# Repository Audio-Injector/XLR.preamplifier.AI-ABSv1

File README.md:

XLR preamplifier

A balanced preamplifier based on the Audio Injector Analogue Breakout Standard v1 (AI-ABS v1)

https://github.com/Audio-Injector/AudioInjector-Analogue-Breakout-Standard

https://www.audioinjector.net/xlr-preamp

https://shop.audioinjector.net/detail/Sound_Cards/Balanced+XLR+preamplifier

Check the single ended (RCA) preamplifier here : https://github.com/Audio-Injector/RCA.preamplifier.AI-ABSv1

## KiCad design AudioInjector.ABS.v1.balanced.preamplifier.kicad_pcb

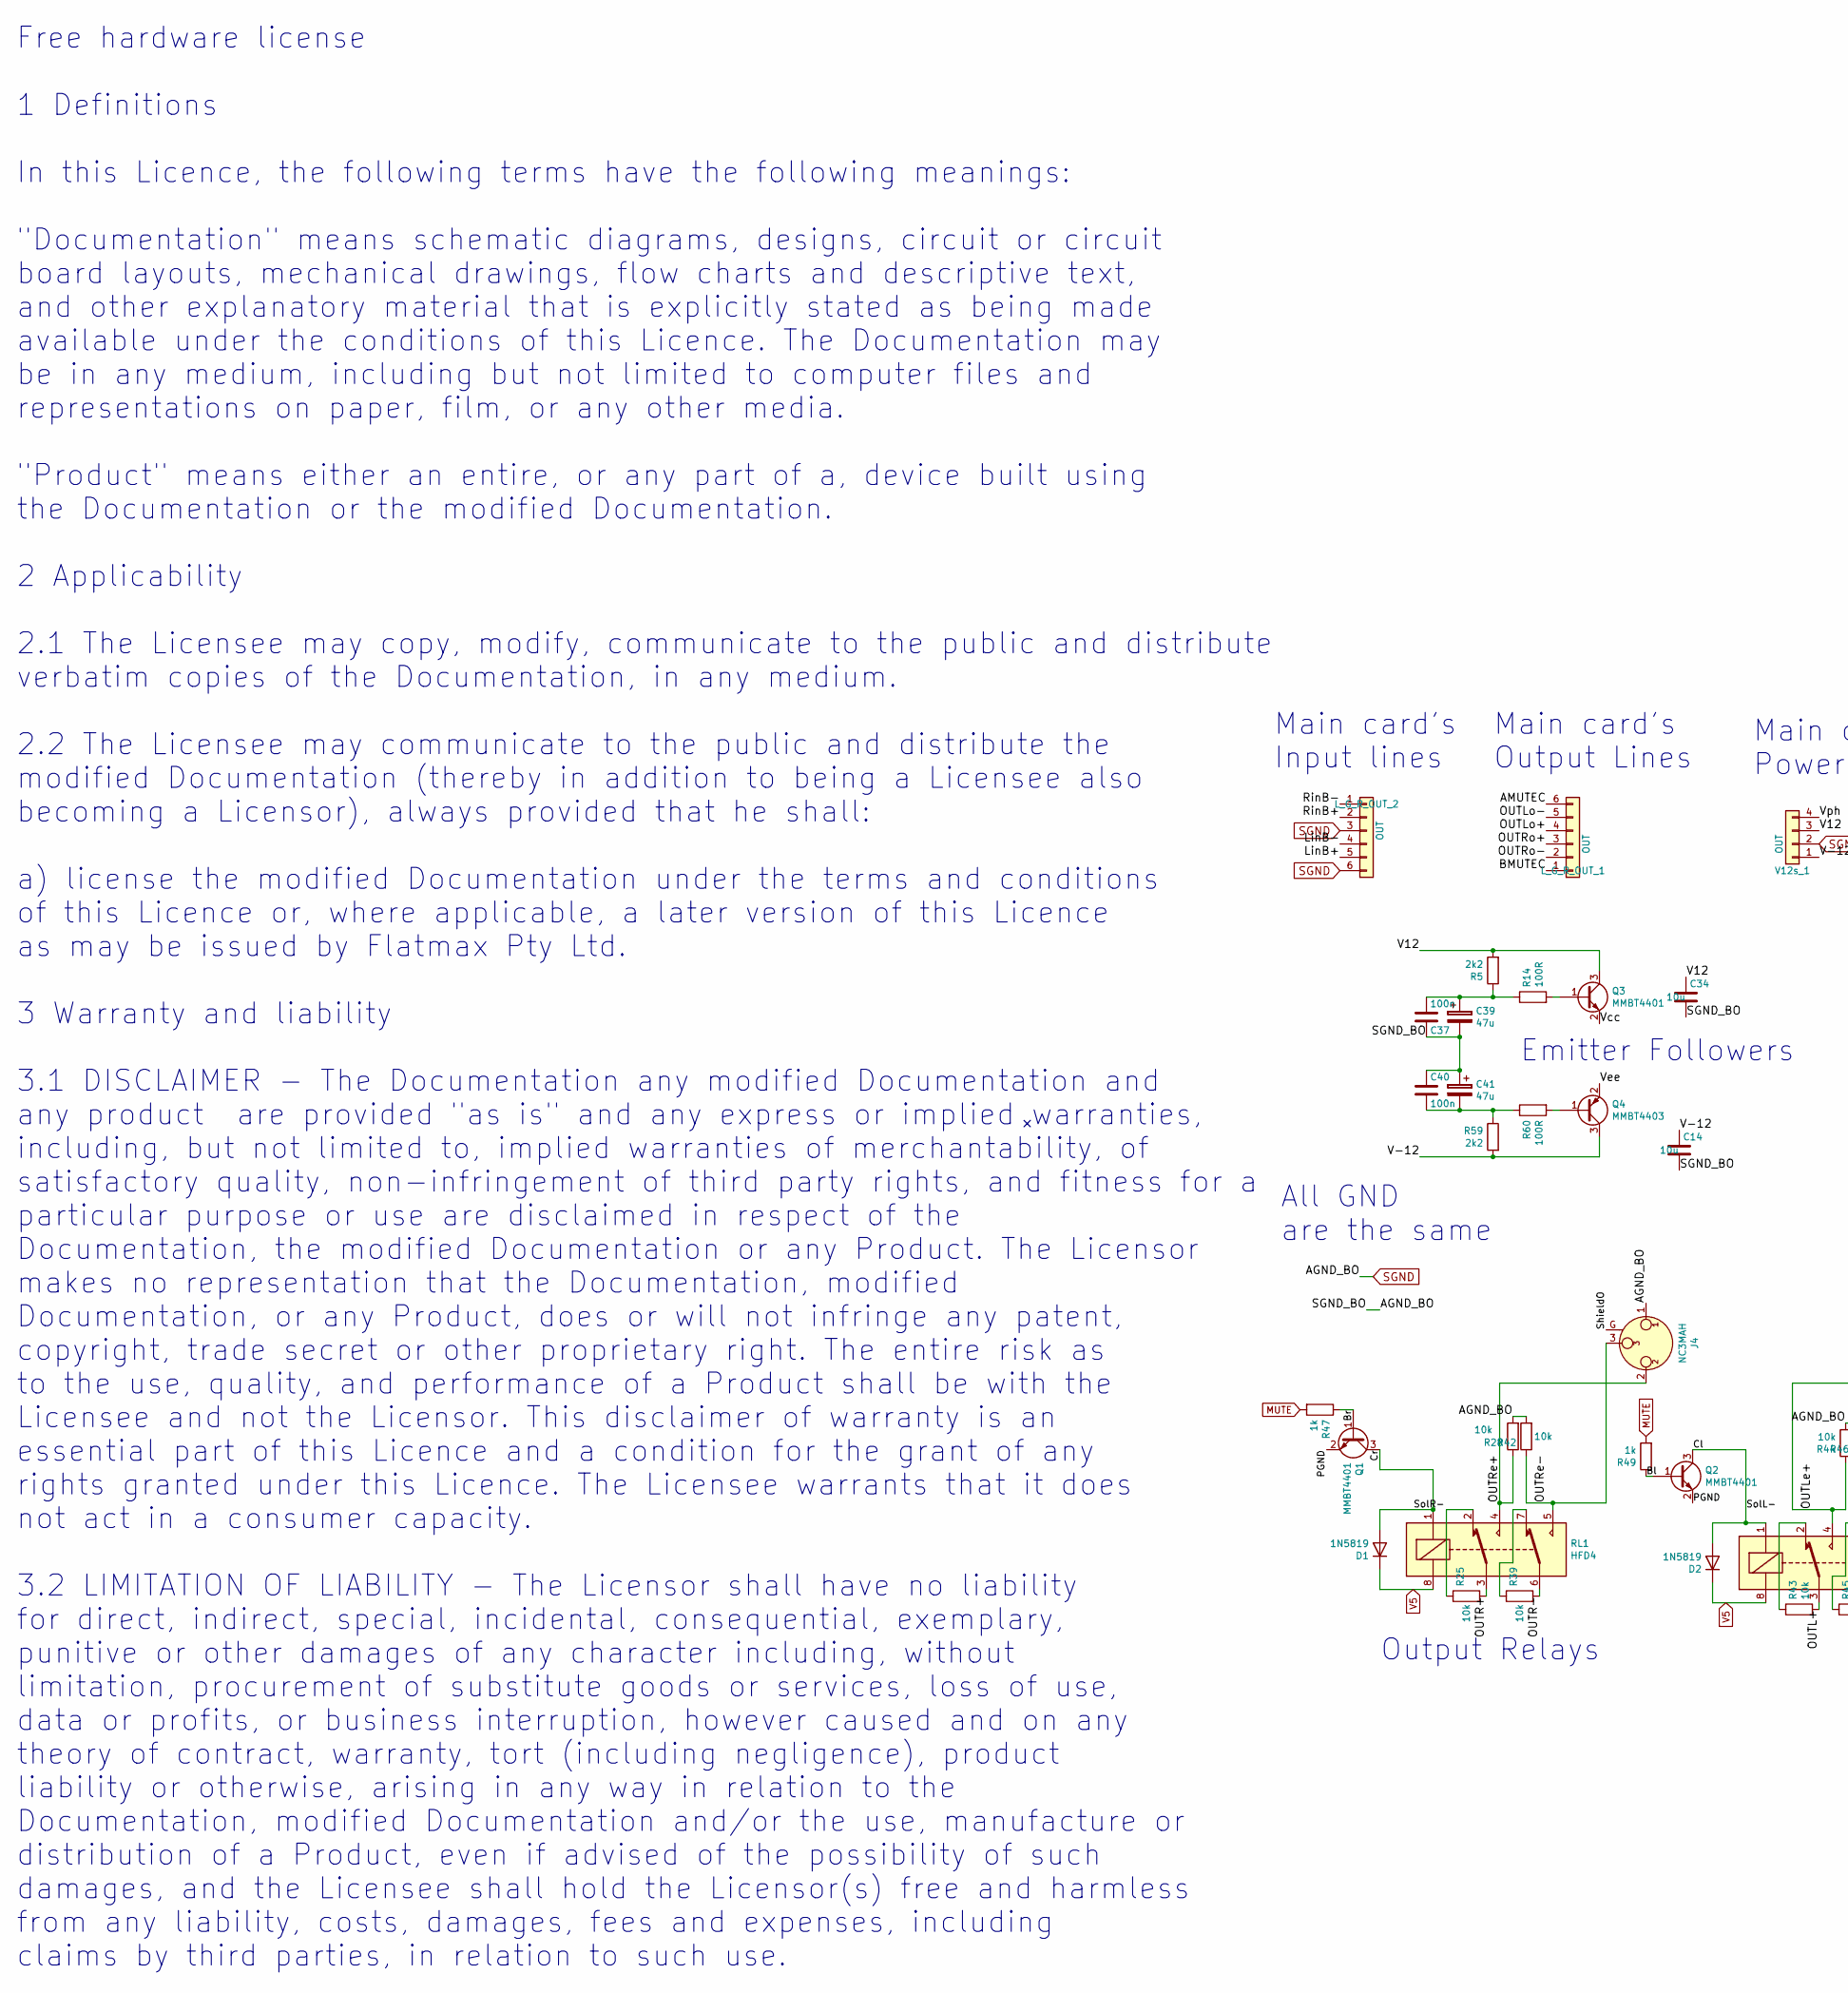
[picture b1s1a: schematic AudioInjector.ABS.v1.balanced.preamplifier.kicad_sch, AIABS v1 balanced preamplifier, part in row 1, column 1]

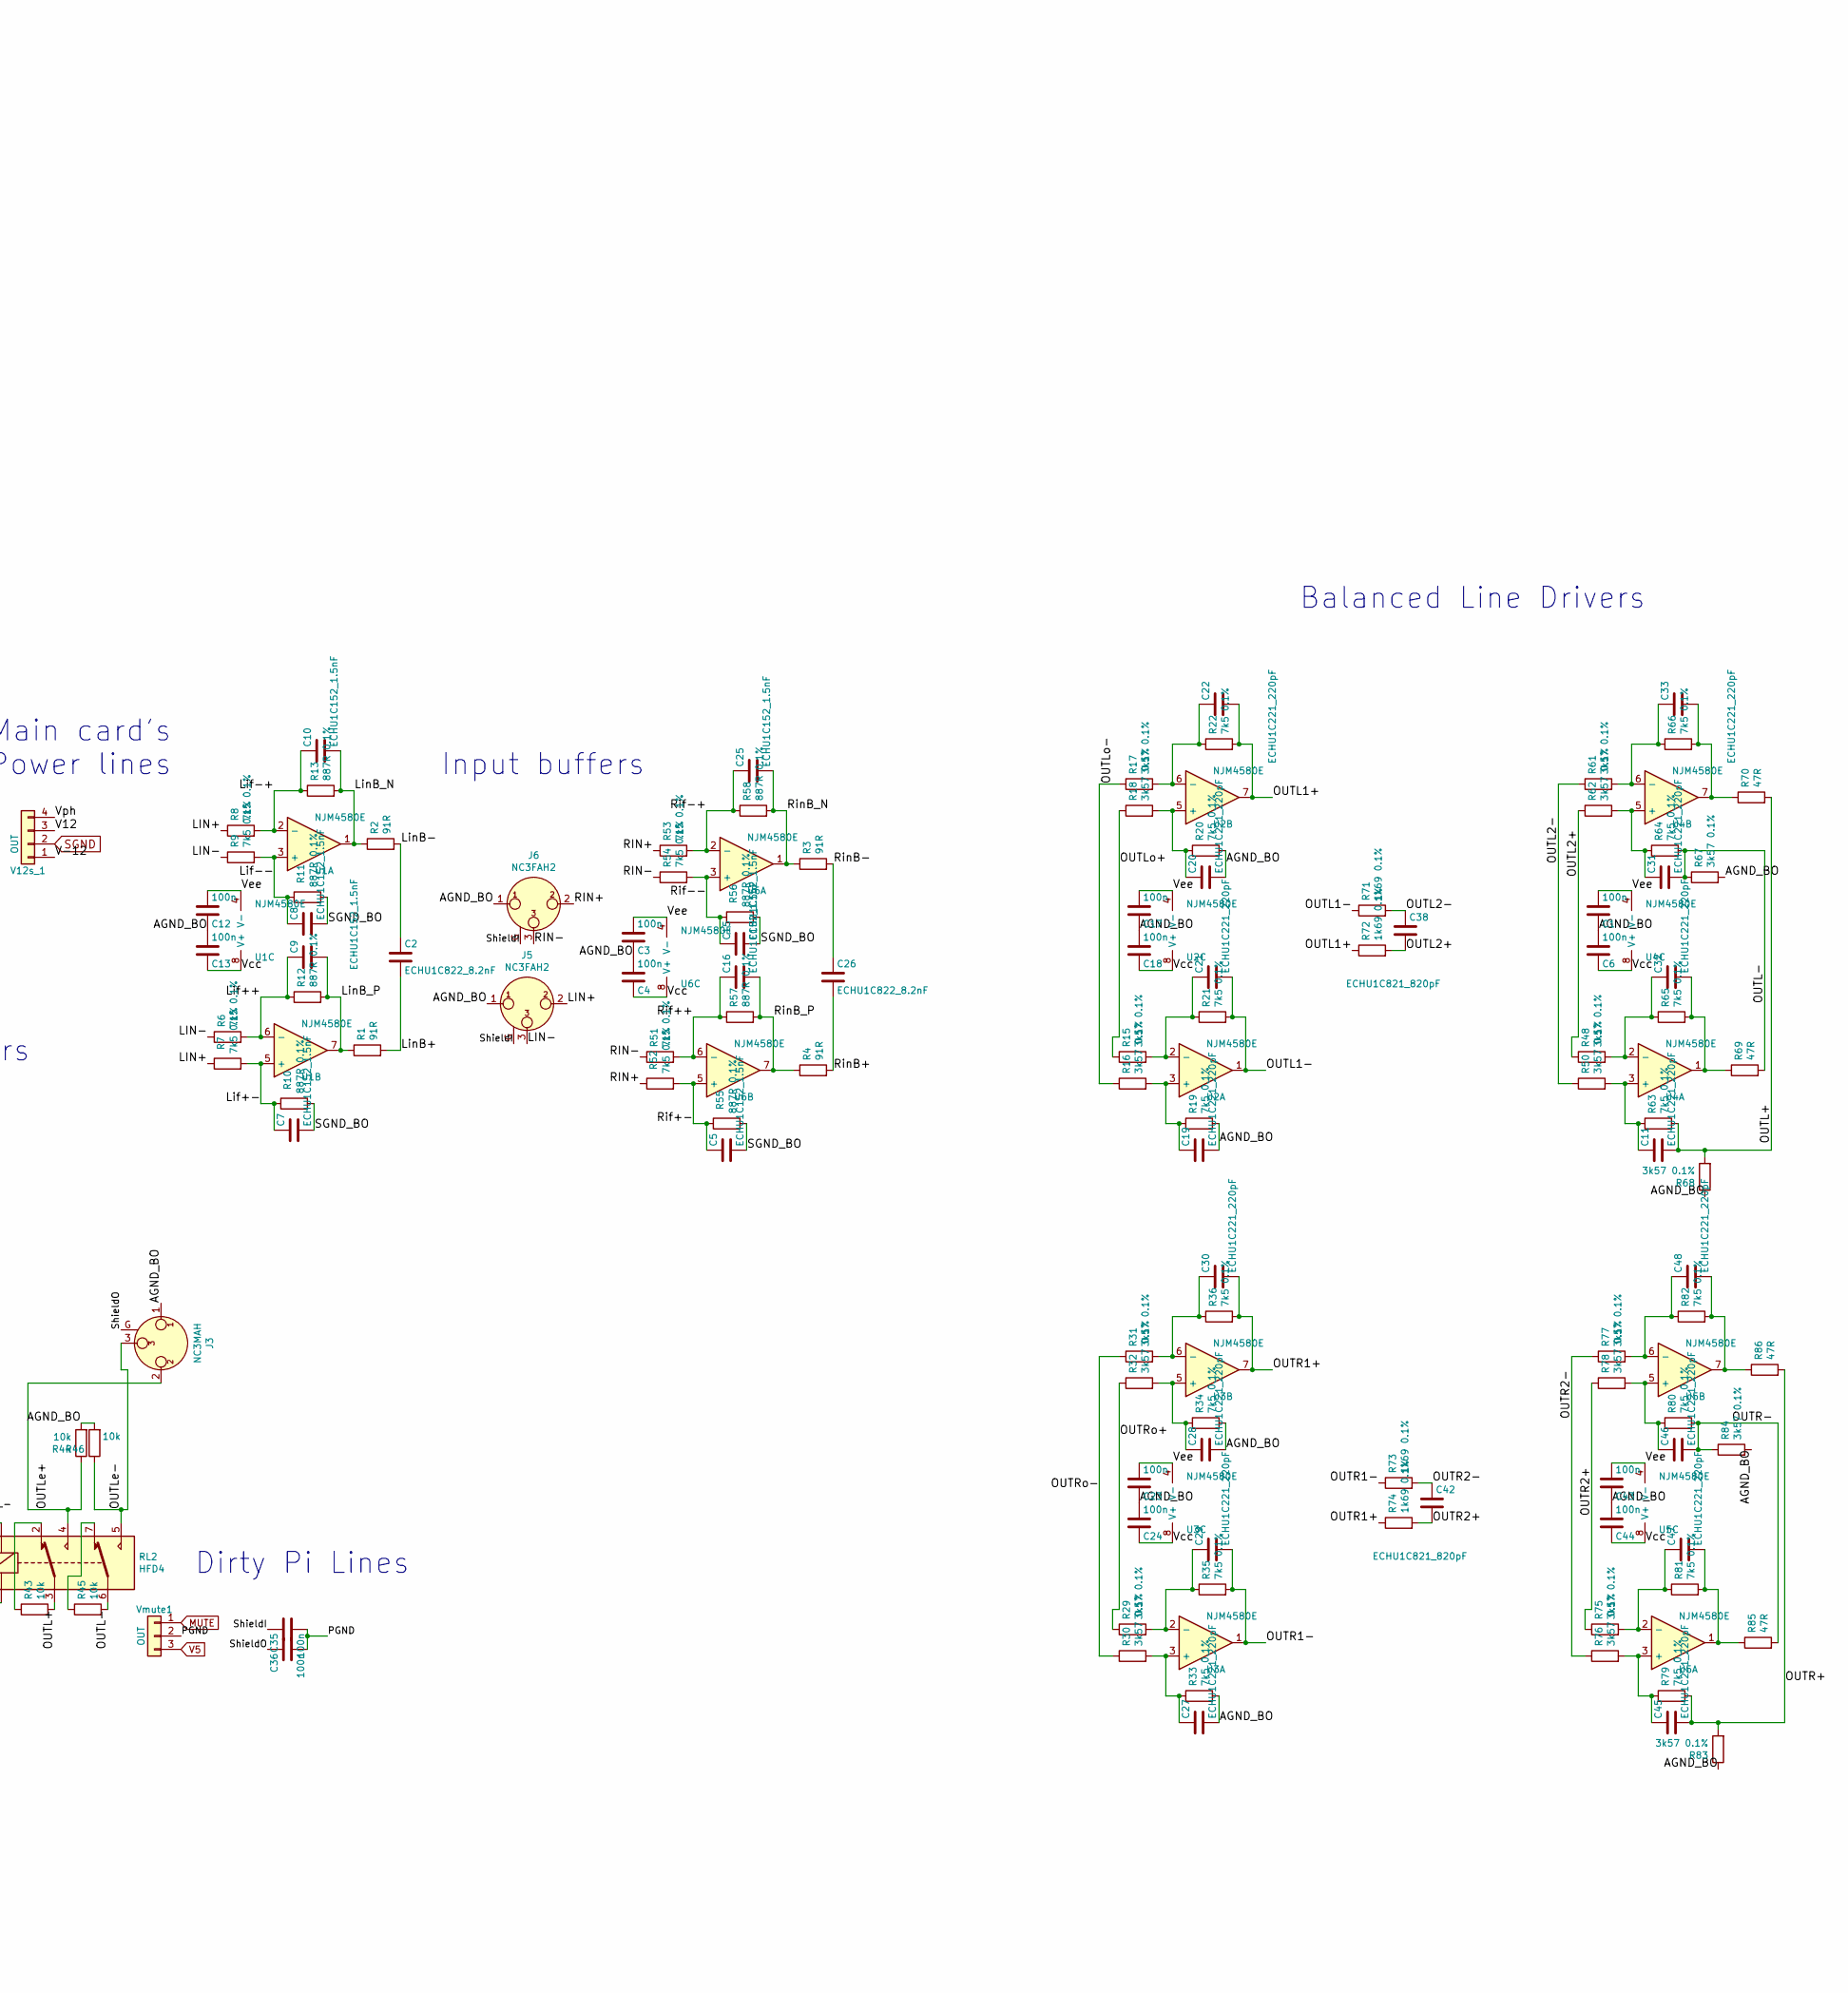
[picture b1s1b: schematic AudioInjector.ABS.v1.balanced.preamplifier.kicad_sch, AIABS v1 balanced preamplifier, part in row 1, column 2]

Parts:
C1, C3, C4, C6, C12, C13, C17, C18, C23, C24, C35, C36, C37, C40, C43, C44: 100n; C_0603_1608Metric
C2, C26: ECHU1C822_8.2nF; C_0805_2012Metric
C5, C7, C8, C9, C10, C15, C16, C25: ECHU1C152_1.5nF; C_0805_2012Metric
C11, C19, C20, C21, C22, C27, C28, C29, C30, C31, C32, C33, C45, C46, C47, C48: ECHU1C221_220pF; C_0805_2012Metric
C14, C34: 10u; C_0805_2012Metric
C38, C42: ECHU1C821_820pF; C_0805_2012Metric
C39, C41: 47u; CP_Elec_6.3x7.7
D1, D2: 1N5819; D_SOD-123
J3, J4: NC3MAH; Jack_XLR_Neutrik_NC3MAH-0_Horizontal
J5, J6: NC3FAH2; Jack_XLR_Neutrik_NC3FAH2_Horizontal
L_G_R_OUT_1, L_G_R_OUT_2: OUT; PinHeader_1x06_P2.54mm_Vertical
Q1, Q2, Q3: MMBT4401; SOT-23
Q4: MMBT4403; SOT-23
R1, R2, R3, R4: 91R; R_0603_1608Metric
R5, R59: 2k2; R_0603_1608Metric
R6, R7, R8, R9, R19, R20, R21, R22, R33, R34, R35, R36, R51, R52, R53, R54, R63, R64, R65, R66, R79, R80, R81, R82: 7k5 0.1%; R_0603_1608Metric
R10, R11, R12, R13, R55, R56, R57, R58: 887R 0.1%; R_0603_1608Metric
R14, R60: 100R; R_0603_1608Metric
R15, R16, R17, R18, R29, R30, R31, R32, R48, R50, R61, R62, R67, R68, R75, R76, R77, R78, R83, R84: 3k57 0.1%; R_0603_1608Metric
R25, R28, R39, R42, R43, R44, R45, R46: 10k; R_0603_1608Metric
R47, R49: 1k; R_0603_1608Metric
R69, R70, R85, R86: 47R; R_0603_1608Metric
R71, R72, R73, R74: 1k69 0.1%; R_0603_1608Metric
RL1, RL2: HFD4; HDF4
U1, U2, U3, U4, U5, U6: NJM4580E; SOIC-8_3.9x4.9mm_P1.27mm
V12s_1: OUT; PinHeader_1x04_P2.54mm_Vertical
Vmute1: OUT; PinHeader_1x03_P2.54mm_Vertical

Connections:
/AMUTEC: L_G_R_OUT_1.6
/BMUTEC: L_G_R_OUT_1.1
/Bl: Q2.1 (B), R49.1
/Br: Q1.1 (B), R47.1
/Cl: D2.2 (A), Q2.3 (C), RL2.1
/Cr: D1.2 (A), Q1.3 (C), RL1.1
/LIN+: J5.2, R7.1, R8.1
/LIN-: J5.3, R6.1, R9.1
/Lif++: C9.1, R6.2, R12.1, U1.6 (-)
/Lif+-: C7.1, R7.2, R10.1, U1.5 (+)
/Lif-+: C10.1, R8.2, R13.1, U1.2 (-)
/Lif--: C8.1, R9.2, R11.1, U1.3 (+)
/LinB+: C2.2, L_G_R_OUT_2.5, R1.2
/LinB-: C2.1, L_G_R_OUT_2.4, R2.2
/LinB_N: C10.2, R2.1, R13.2, U1.1
/LinB_P: C9.2, R1.1, R12.2, U1.7
/OUTL1+: C22.2, R22.2, R72.1, U2.7
/OUTL1-: C21.2, R21.2, R71.1, U2.1
/OUTL2+: C38.2, R48.1, R62.1, R72.2
/OUTL2-: C38.1, R50.1, R61.1, R71.2
/OUTL+: C11.2, R43.2, R63.2, R68.2, R70.2, RL2.3
/OUTL-: C31.2, R45.2, R64.2, R67.1, R69.2, RL2.6
/OUTLe+: J3.2, R44.1, RL2.4
/OUTLe-: J3.3, R46.1, RL2.5
/OUTLo+: L_G_R_OUT_1.4, R15.1, R18.1
/OUTLo-: L_G_R_OUT_1.5, R16.1, R17.1
/OUTR1+: C30.2, R36.2, R74.1, U3.7
/OUTR1-: C29.2, R35.2, R73.1, U3.1
/OUTR2+: C42.2, R74.2, R75.1, R78.1
/OUTR2-: C42.1, R73.2, R76.1, R77.1
/OUTR+: C45.2, R25.2, R79.2, R83.2, R86.2, RL1.3
/OUTR-: C46.2, R39.2, R80.2, R84.1, R85.2, RL1.6
/OUTRe+: J4.2, R28.1, RL1.4
/OUTRe-: J4.3, R42.1, RL1.5
/OUTRo+: L_G_R_OUT_1.3, R29.1, R32.1
/OUTRo-: L_G_R_OUT_1.2, R30.1, R31.1
/PGND: C35.2, C36.2, Q1.2 (E), Q2.2 (E), Vmute1.2
/RIN+: J6.2, R52.1, R53.1
/RIN-: J6.3, R51.1, R54.1
/Rif++: C16.1, R51.2, R57.1, U6.6 (-)
/Rif+-: C5.1, R52.2, R55.1, U6.5 (+)
/Rif-+: C25.1, R53.2, R58.1, U6.2 (-)
/Rif--: C15.1, R54.2, R56.1, U6.3 (+)
/RinB+: C26.2, L_G_R_OUT_2.2, R4.2
/RinB-: C26.1, L_G_R_OUT_2.1, R3.2
/RinB_N: C25.2, R3.1, R58.2, U6.1
/RinB_P: C16.2, R4.1, R57.2, U6.7
/ShieldI: C35.1, J5.G, J6.G
/ShieldO: C36.1, J3.G, J4.G
/V12: C34.1, Q3.3 (C), R5.2, V12s_1.3
/V-12: C14.1, Q4.3 (C), R59.2, V12s_1.1
/Vcc: C4.1, C6.1, C13.1, C18.1, C24.1, C44.1, Q3.2 (E), U1.8 (V+), U2.8 (V+), U3.8 (V+), U4.8 (V+), U5.8 (V+), U6.8 (V+)
/Vee: C1.2, C3.2, C12.2, C17.2, C23.2, C43.2, Q4.2 (E), U1.4 (V-), U2.4 (V-), U3.4 (V-), U4.4 (V-), U5.4 (V-), U6.4 (V-)
/Vph: V12s_1.4
MUTE: R47.2, R49.2, Vmute1.1
unnamed: C11.1, R50.2, R63.1, U4.3 (+)
unnamed: C19.1, R16.2, R19.1, U2.3 (+)
unnamed: C20.1, R18.2, R20.1, U2.5 (+)
unnamed: C21.1, R15.2, R21.1, U2.2 (-)
unnamed: C22.1, R17.2, R22.1, U2.6 (-)
unnamed: C27.1, R30.2, R33.1, U3.3 (+)
unnamed: C28.1, R32.2, R34.1, U3.5 (+)
unnamed: C29.1, R29.2, R35.1, U3.2 (-)
unnamed: C30.1, R31.2, R36.1, U3.6 (-)
unnamed: C31.1, R62.2, R64.1, U4.5 (+)
unnamed: C32.1, R48.2, R65.1, U4.2 (-)
unnamed: C32.2, R65.2, R69.1, U4.1
unnamed: C33.1, R61.2, R66.1, U4.6 (-)
unnamed: C33.2, R66.2, R70.1, U4.7
unnamed: C37.2, C39.1, R5.1, R14.1
unnamed: C40.2, C41.2, R59.1, R60.1
unnamed: C45.1, R76.2, R79.1, U5.3 (+)
unnamed: C46.1, R78.2, R80.1, U5.5 (+)
unnamed: C47.1, R75.2, R81.1, U5.2 (-)
unnamed: C47.2, R81.2, R85.1, U5.1
unnamed: C48.1, R77.2, R82.1, U5.6 (-)
unnamed: C48.2, R82.2, R86.1, U5.7
unnamed: Q3.1 (B), R14.2
unnamed: Q4.1 (B), R60.2
unnamed: R25.1, RL1.2
unnamed: R39.1, RL1.7
unnamed: R43.1, RL2.2
unnamed: R45.1, RL2.7
SGND: C1.1, C3.1, C4.2, C5.2, C6.2, C7.2, C8.2, C12.1, C13.2, C14.2, C15.2, C17.1, C18.2, C19.2, C20.2, C23.1, C24.2, C27.2, C28.2, C34.2, C37.1, C39.2, C40.1, C41.1, C43.1, C44.2, J3.1, J4.1, J5.1, J6.1, L_G_R_OUT_2.3, L_G_R_OUT_2.6, R10.2, R11.2, R19.2, R20.2, R28.2, R33.2, R34.2, R42.2, R44.2, R46.2, R55.2, R56.2, R67.2, R68.1, R83.1, R84.2, V12s_1.2
V5: D1.1 (K), D2.1 (K), RL1.8, RL2.8, Vmute1.3

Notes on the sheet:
All GND are the same
Input buffers
Free hardware license 1 Definitions In this Licence, the following terms have the following meanings: "Documentation" means schematic diagrams, designs, circuit or circuit board layouts, mechanical drawings, flow charts and descriptive text, and other explanatory material that is explicitly stated 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
Output Relays
Dirty Pi Lines
Main card's Output Lines
Main card's Input lines
Balanced Line Drivers
Main card's Power lines
Emitter Followers

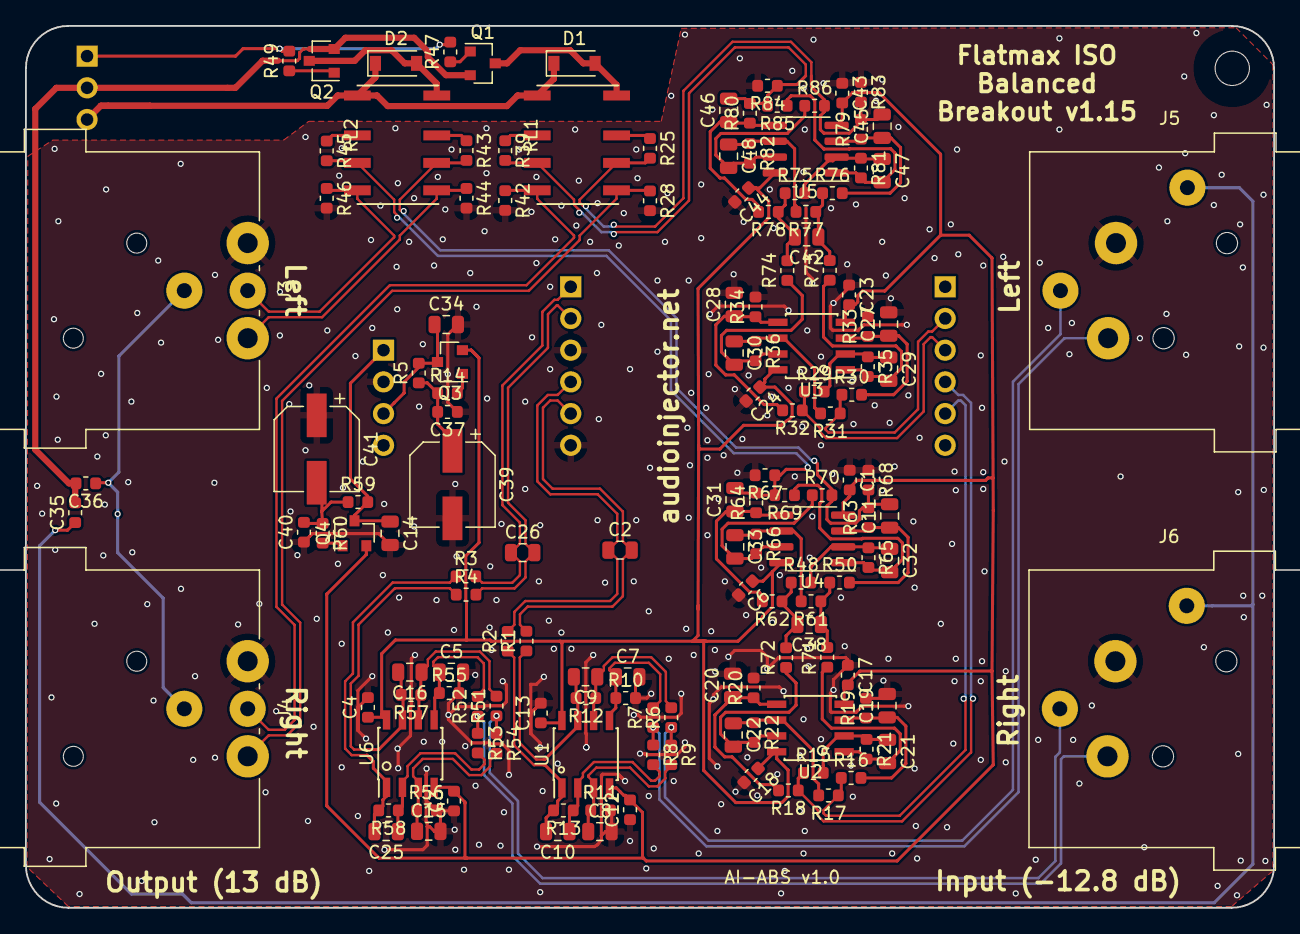
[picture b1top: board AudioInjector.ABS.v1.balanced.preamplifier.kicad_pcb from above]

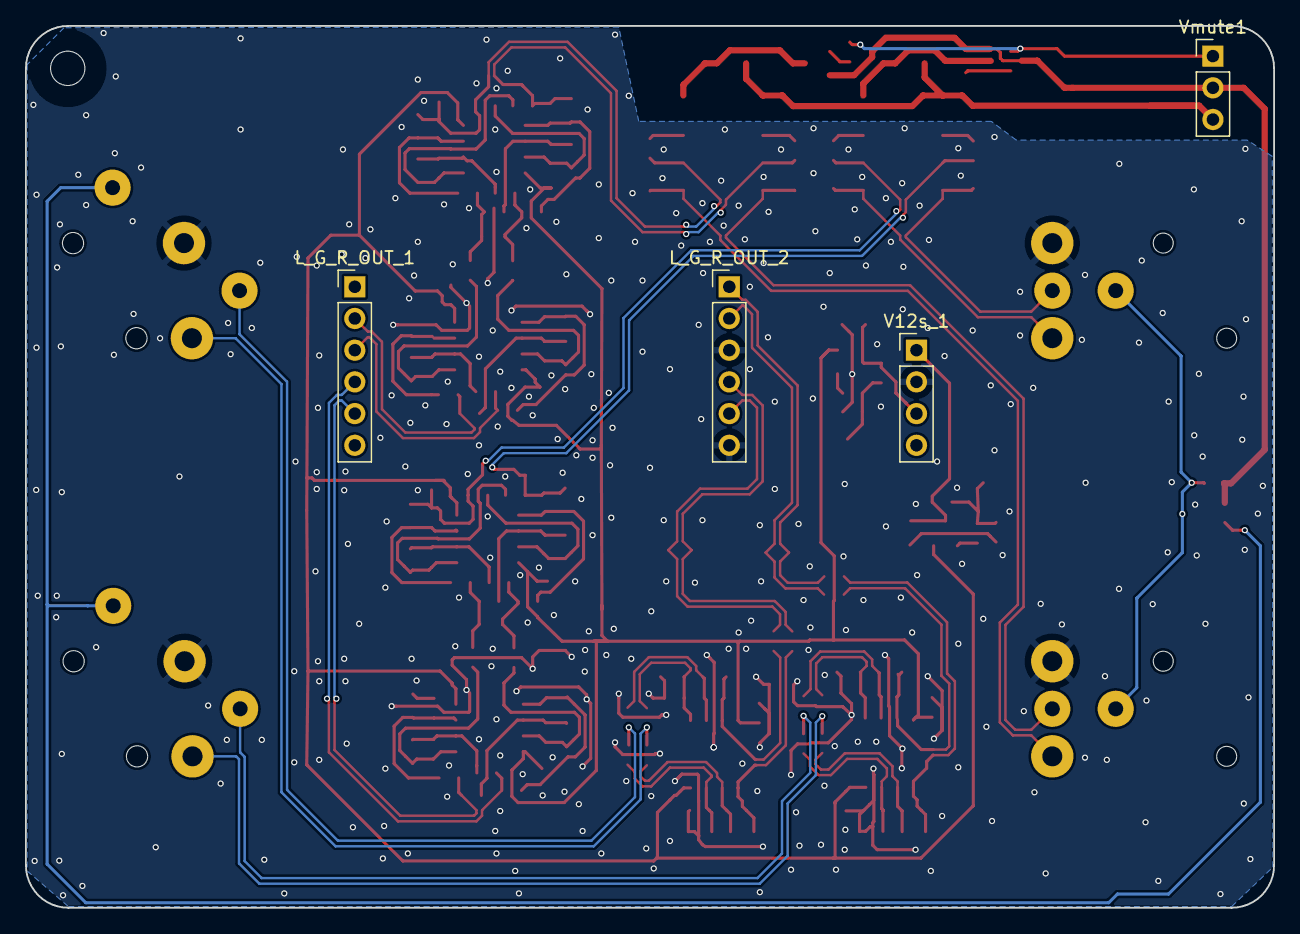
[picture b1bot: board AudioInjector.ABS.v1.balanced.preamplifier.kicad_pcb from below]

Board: 4 copper layers, 100.0 x 70.7 mm, 148 parts (4 on the bottom side), 82 nets.

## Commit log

2022-08-31 v1.15
2022-08-31 added a link to the RCA preamplifier
2022-08-31 Generated and added the gerber files.

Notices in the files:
AudioInjector.ABS.v1.balanced.preamplifier.kicad_pcb:
available under the conditions of this Licence. The Documentation may
rights granted under this Licence. The Licensee warrants that it does
